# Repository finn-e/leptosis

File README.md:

# Leptosis - Ultra Flat PG1316 Split Keyboard

"Leptos" stands for "flat" in greek, added with the suffix is, it forms the word "Leptosis", signifying the most flat. This represents my long lasting desire for an real flat keyboard that is portable and light. The name is also quite similar to the latin word "levitatio", signifying levitation and thus light. (I'm bad at naming things lol)

## What is this?

Leptosis is an ultra flat split bluetooth keyboard. It's thickness will be ~7.5mm, and employs the compact miryoku layout. Using an onboard nrf module, it achieves an ultra long battery life.

| Left | Right |
| ---- | ----- |
|  |  |

## Features
- Ultra long battery life (~4 months for central and 1 year for peripheral)
- Ultra thin (7.5mm)
- Compact (13.2x9.2cm)
- Custom battery management and optimization
- Embedded nrf52 mcu
- ZMK bluetooth

## Fabrication

You can either use PCBA to fabricate the PCB, or reflow it yourself. I highly discurrage you to reflow the yourself if you haven't reflowed a aQFN package before - it's a nightmare to get right.

The PCB files are in the `hardware` directory, you need to buy one pcb for the right and the left. There is also a V-Cut panneled version in `hardware/panel`. It uses JLCPCB's 1.2mm JLC04121H-7628 stackup. Other stackups would require re-tuning of the USB data lines and antenna feed trace.

The case is in the `CAD` directory. Print out all `.step` files.

The software is in the `firmware`. Leptosis uses ZMK, allowing ultra long battery life.

After fabrication, solder on some jumpers onto the 4 test pads, and connect it to a JTAG connector (I'm using the ST-LINK). Download the bootloader from the newest action [here](https://github.com/cheyao/Adafruit_nRF52_Bootloader/actions) and unzip it.

For stlink, install openocd and run the following commands:

```zsh
openocd -f /usr/share/openocd/scripts/interface/stlink.cfg -f /usr/share/openocd/scripts/target/nrf52.cfg -c 'program <path_to_bootloader>.hex verify reset; shutdown;'
```

For other JTAG connectors, please refer to your own documentation.

Now plug in a USB-C cable, and you should see a mass storage device called `LEPTOSIS`.

Download the ZMK config from this repo: https://github.com/cheyao/zmk-config/actions, drag the utf file to the mass storage device and you are done!

## Misc

Liked this project? Drop a star and check out my [other Icepi Zero project](https://www.crowdsupply.com/icy-electronics/icepi-zero/)!

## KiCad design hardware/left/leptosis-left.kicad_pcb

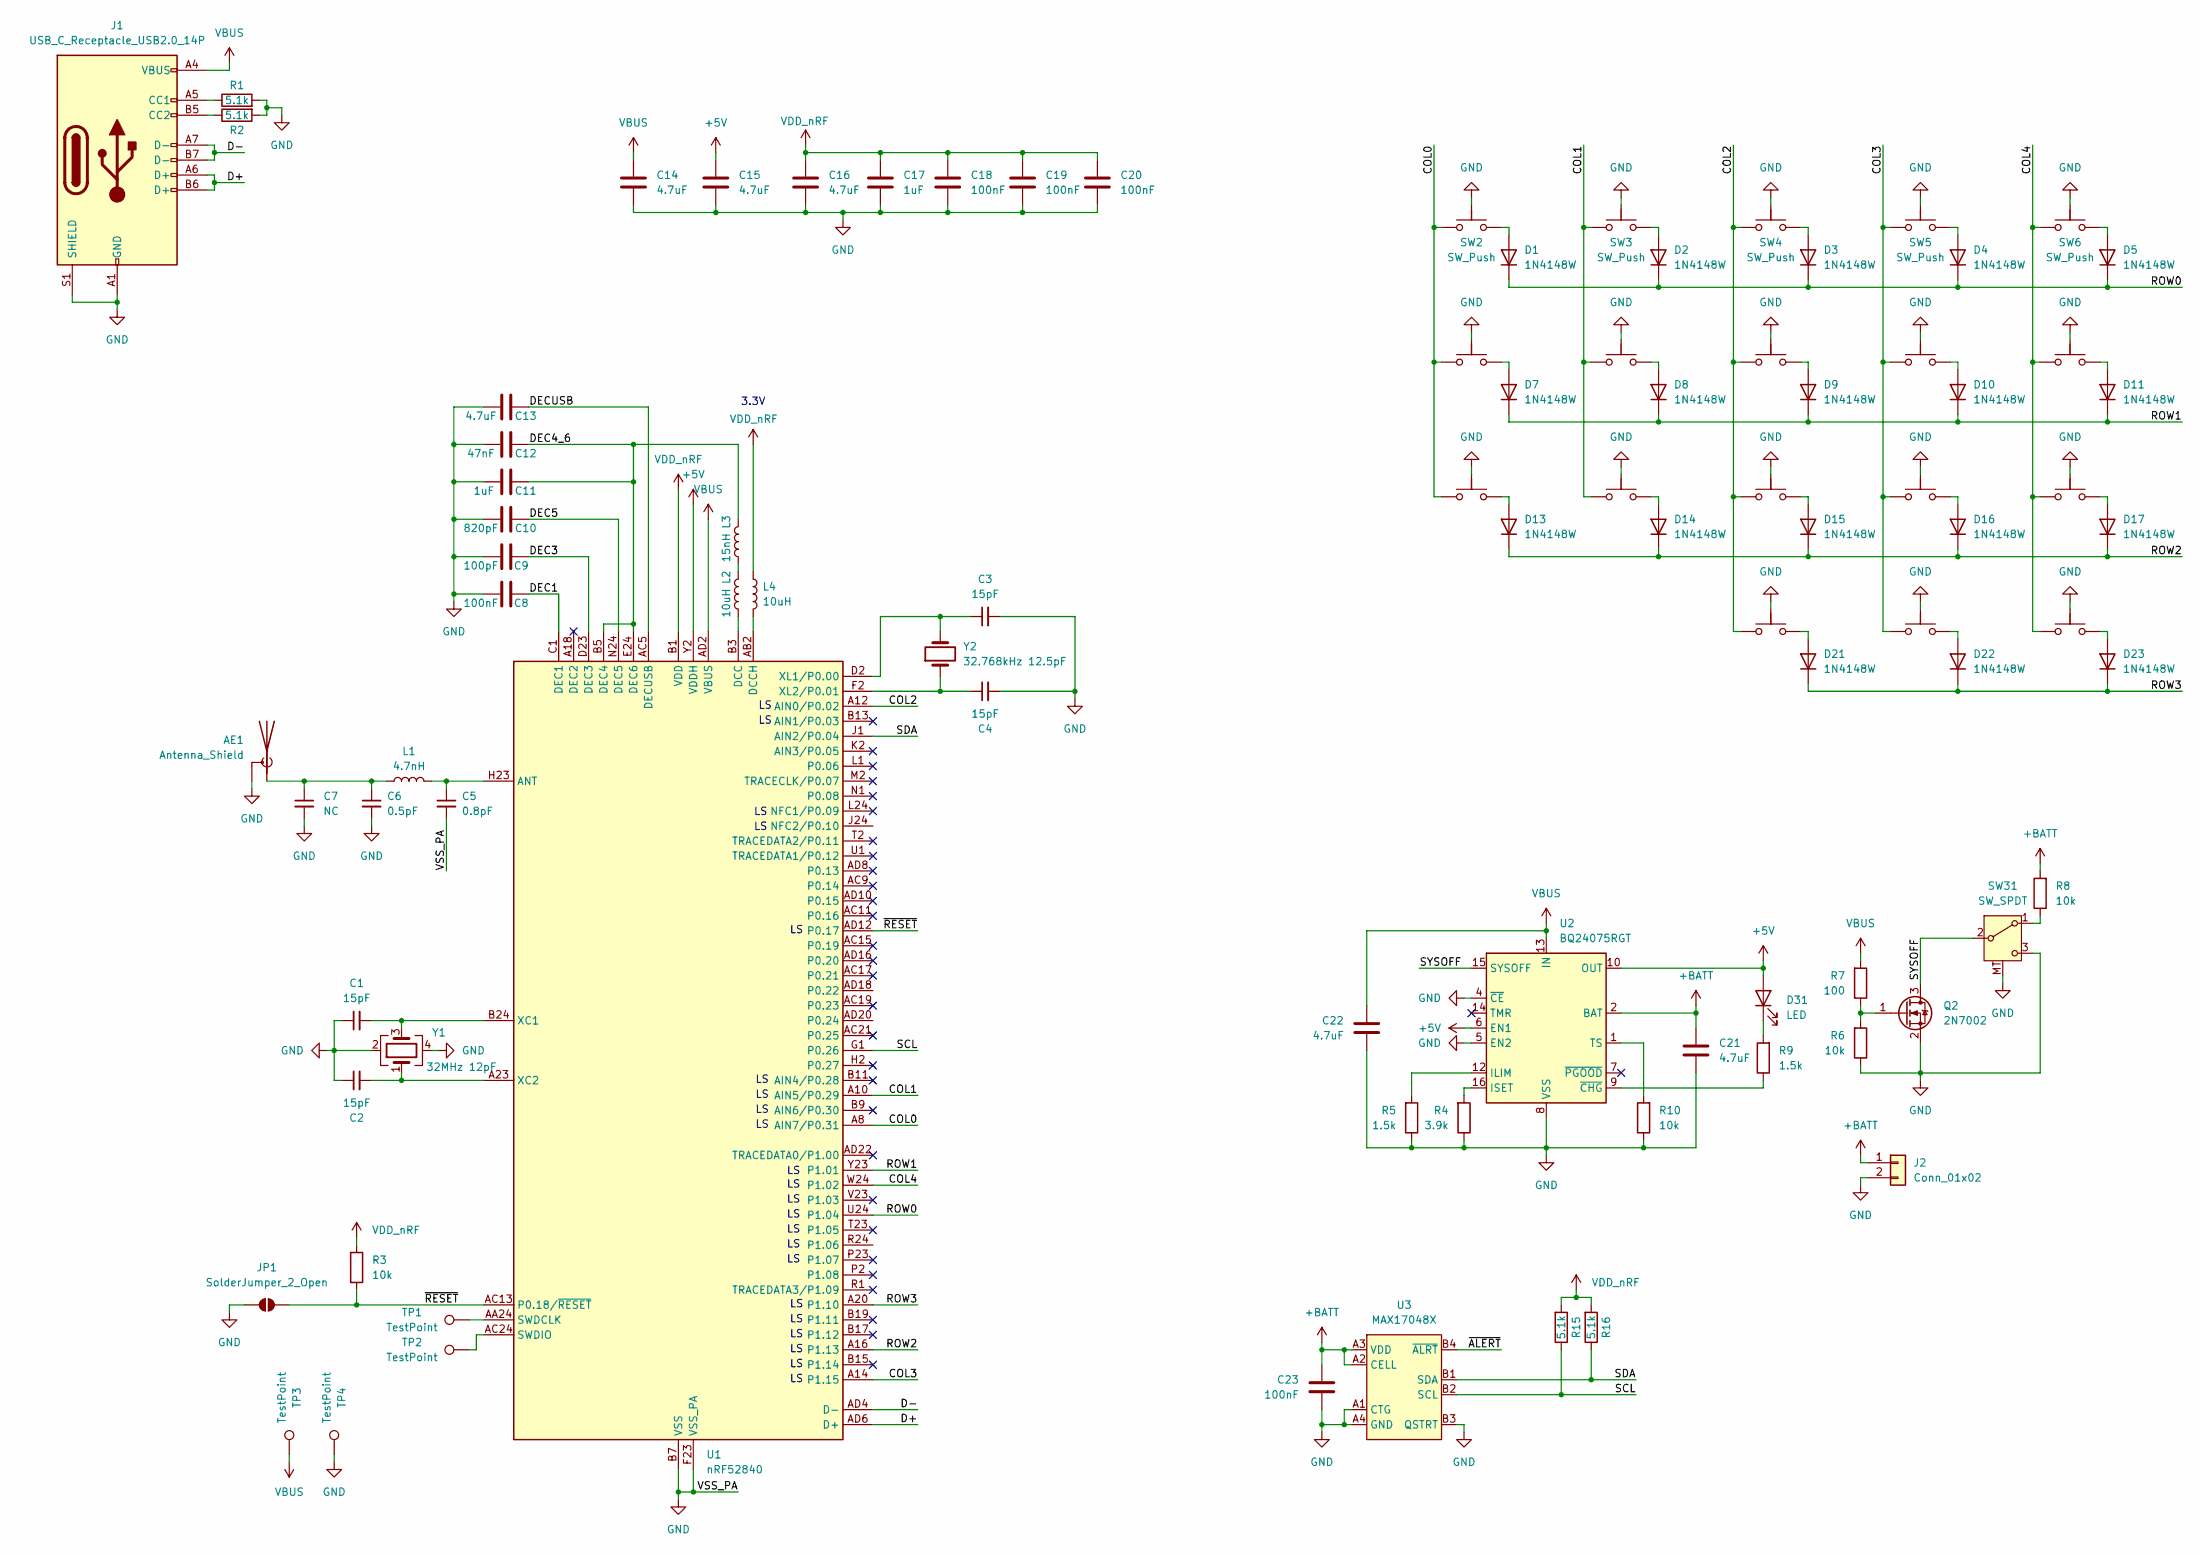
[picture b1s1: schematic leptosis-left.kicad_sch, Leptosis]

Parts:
AE1: Antenna_Shield; Texas_SWRA117D_2.4GHz_Left
C1, C2, C3, C4: 15pF; C_0402_1005Metric; LCSC Part # C1548
C5: 0.8pF; C_0402_1005Metric; LCSC Part # C41361068
C6: 0.5pF; C_0402_1005Metric; LCSC Part # C76912
C7: NC; C_0402_1005Metric
C8, C18, C19, C20, C23: 100nF; C_0402_1005Metric; LCSC Part # C1525
C9: 100pF; C_0402_1005Metric; LCSC Part # C1546
C10: 820pF; C_0402_1005Metric; LCSC Part # C107031
C11, C17: 1uF; C_0603_1608Metric; LCSC Part # C15849
C12: 47nF; C_0402_1005Metric; LCSC Part # C272875
C13, C14, C15, C16, C21, C22: 4.7uF; C_0603_1608Metric; LCSC Part # C19666
D1, D2, D3, D4, D5, D7, D8, D9, D10, D11, D13, D14, D15, D16, D17, D21, D22, D23: 1N4148W; D_SOD-123; LCSC Part # C81598
D31: LED; LED_0603_1608Metric_Pad1.05x0.95mm_HandSolder; LCSC Part # C2290
J1: USB_C_Receptacle_USB2.0_14P; USB_C_Receptacle_HRO_TYPE-C-31-M-14; LCSC Part # C223907
J2: Conn_01x02; PinSocket_1x02_P2.54mm_Vertical
JP1: SolderJumper_2_Open; SolderJumper-2_P1.3mm_Open_RoundedPad1.0x1.5mm
L1: 4.7nH; L_0402_1005Metric; LCSC Part # C86065
L2, L4: 10uH; L_0603_1608Metric; LCSC Part # C86083
L3: 15nH; L_0402_1005Metric; LCSC Part # C86059
Q2: 2N7002; SOT-23; LCSC Part # C8545
R1, R2, R15, R16: 5.1k; R_0402_1005Metric_Pad0.72x0.64mm_HandSolder; LCSC Part # C25905
R3, R6, R8, R10: 10k; R_0402_1005Metric_Pad0.72x0.64mm_HandSolder; LCSC Part # C25744
R4: 3.9k; R_0402_1005Metric_Pad0.72x0.64mm_HandSolder; LCSC Part # C131467
R5, R9: 1.5k; R_0402_1005Metric_Pad0.72x0.64mm_HandSolder; LCSC Part # C25867
R7: 100; R_0402_1005Metric_Pad0.72x0.64mm_HandSolder; LCSC Part # C25076
SW2, SW3, SW4, SW5, SW6, SW8, SW9, SW10, SW11, SW12, SW14, SW15, SW16, SW17, SW18, SW22, SW23, SW24: SW_Push; SW_PG1316S
SW31: SW_SPDT; Switch_Sink_MINI_MSK12CO2; LCSC Part # C2681570
TP1, TP2, TP3, TP4: TestPoint; TestPoint_Pad_D1.5mm
U1: nRF52840; Nordic_AQFN-73-1EP_7x7mm_P0.5mm; LCSC Part # C190794
U2: BQ24075RGT; VQFN-16-1EP_3x3mm_P0.5mm_EP1.6x1.6mm; LCSC Part # C15464
U3: MAX17048X; WLP-8_1.67x0.93_P0.4; LCSC Part # C7497002
Y1: 32MHz 12pF; Crystal_SMD_2016-4Pin_2.0x1.6mm; LCSC Part # C2682773
Y2: 32.768kHz 12.5pF; Crystal_SMD_3215-2Pin_3.2x1.5mm; LCSC Part # C5213671

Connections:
+5V: C15.1, D31.2 (A), U1.Y2 (VDDH), U2.6 (EN1), U2.10 (OUT), U2.11 (OUT)
+BATT: C21.1, C23.1, J2.1, R8.2, U2.2 (BAT), U2.3 (BAT), U3.A2 (CELL), U3.A3 (VDD)
/COL0: SW2.1, SW8.1, SW14.1, U1.A8 (AIN7/P0.31)
/COL1: SW3.1, SW9.1, SW15.1, U1.A10 (AIN5/P0.29)
/COL2: SW4.1, SW10.1, SW16.1, SW22.1, U1.A12 (AIN0/P0.02)
/COL3: SW5.1, SW11.1, SW17.1, SW23.1, U1.A14 (P1.15)
/COL4: SW6.1, SW12.1, SW18.1, SW24.1, U1.W24 (P1.02)
/D+: J1.A6 (D+), J1.B6 (D+), U1.AD6 (D+)
/D-: J1.A7 (D-), J1.B7 (D-), U1.AD4 (D-)
/DEC1: C8.2, U1.C1 (DEC1)
/DEC3: C9.2, U1.D23 (DEC3)
/DEC4_6: C11.2, C12.2, L3.2, U1.B5 (DEC4), U1.E24 (DEC6)
/DEC5: C10.2, U1.N24 (DEC5)
/DECUSB: C13.2, U1.AC5 (DECUSB)
/ROW0: D1.1 (K), D2.1 (K), D3.1 (K), D4.1 (K), D5.1 (K), U1.U24 (P1.04)
/ROW1: D7.1 (K), D8.1 (K), D9.1 (K), D10.1 (K), D11.1 (K), U1.Y23 (P1.01)
/ROW2: D13.1 (K), D14.1 (K), D15.1 (K), D16.1 (K), D17.1 (K), U1.A16 (P1.13)
/ROW3: D21.1 (K), D22.1 (K), D23.1 (K), U1.A20 (P1.10)
/SCL: R15.1, U1.G1 (P0.26), U3.B2 (SCL)
/SDA: R16.1, U1.J1 (AIN2/P0.04), U3.B1 (SDA)
/SYSOFF: Q2.3 (D), SW31.2 (B), U2.15 (SYSOFF)
/~ALERT: U3.B4 (~ALRT)
/~RESET: JP1.2 (B), R3.2, U1.AC13 (P0.18/~RESET), U1.AD12 (P0.17)
GND: AE1.2 (Shield), C1.1, C2.1, C3.2, C4.2, C5.2, C6.2, C7.2, C8.1, C9.1, C10.1, C11.1, C12.1, C13.1, C14.2, C15.2, C16.2, C17.2, C18.2, C19.2, C20.2, C21.2, C22.2, C23.2, J1.A1 (GND), J1.A12 (GND), J1.B1 (GND), J1.B12 (GND), J1.S1 (SHIELD), J2.2, JP1.1 (A), Q2.2 (S), R1.2, R2.2, R4.1, R5.1, R6.1, R10.1, SW2.MP, SW3.MP, SW4.MP, SW5.MP, SW6.MP, SW8.MP, SW9.MP, SW10.MP, SW11.MP, SW12.MP, SW14.MP, SW15.MP, SW16.MP, SW17.MP, SW18.MP, SW22.MP, SW23.MP, SW24.MP, SW31.3 (C), SW31.MT, TP4.1, U1.B7 (VSS), U1.EP (VSS), U1.F23 (VSS_PA), U2.4 (~CE), U2.5 (EN2), U2.8 (VSS), U2.17 (VSS), U3.A1 (CTG), U3.A4 (GND), U3.B3 (QSTRT), Y1.2, Y1.4
unnamed: AE1.1 (A), C6.1, C7.1, L1.1
unnamed: D1.2 (A), SW2.2
unnamed: D2.2 (A), SW3.2
unnamed: D3.2 (A), SW4.2
unnamed: D4.2 (A), SW5.2
unnamed: D5.2 (A), SW6.2
unnamed: D7.2 (A), SW8.2
unnamed: D8.2 (A), SW9.2
unnamed: D9.2 (A), SW10.2
unnamed: D10.2 (A), SW11.2
unnamed: D11.2 (A), SW12.2
unnamed: D13.2 (A), SW14.2
unnamed: D14.2 (A), SW15.2
unnamed: D15.2 (A), SW16.2
unnamed: D16.2 (A), SW17.2
unnamed: D17.2 (A), SW18.2
unnamed: D21.2 (A), SW22.2
unnamed: D22.2 (A), SW23.2
unnamed: D23.2 (A), SW24.2
unnamed: D31.1 (K), R9.2
unnamed: J1.A5 (CC1), R1.1
unnamed: J1.B5 (CC2), R2.1
unnamed: L2.2, L3.1
unnamed: Q2.1 (G), R6.2, R7.1
unnamed: R8.1, SW31.1 (A)
unnamed: C5.1, L1.2, U1.H23 (ANT)
unnamed: L2.1, U1.B3 (DCC)
unnamed: L4.1, U1.AB2 (DCCH)
unnamed: TP1.1, U1.AA24 (SWDCLK)
unnamed: TP2.1, U1.AC24 (SWDIO)
unnamed: C1.2, U1.B24 (XC1), Y1.3
unnamed: C2.2, U1.A23 (XC2), Y1.1
unnamed: C3.1, U1.D2 (XL1/P0.00), Y2.2
unnamed: C4.1, U1.F2 (XL2/P0.01), Y2.1
unnamed: R5.2, U2.12 (ILIM)
unnamed: R4.2, U2.16 (ISET)
unnamed: R10.2, U2.1 (TS)
unnamed: R9.1, U2.9 (~CHG)
VBUS: C14.1, C22.1, J1.A4 (VBUS), J1.A9 (VBUS), J1.B4 (VBUS), J1.B9 (VBUS), R7.2, TP3.1, U1.AD2 (VBUS), U2.13 (IN)
VDD_nRF: C16.1, C17.1, C18.1, C19.1, C20.1, L4.2, R3.1, R15.2, R16.2, U1.A22 (VDD), U1.AD14 (VDD), U1.AD23 (VDD), U1.B1 (VDD), U1.W1 (VDD)

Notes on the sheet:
3.3V

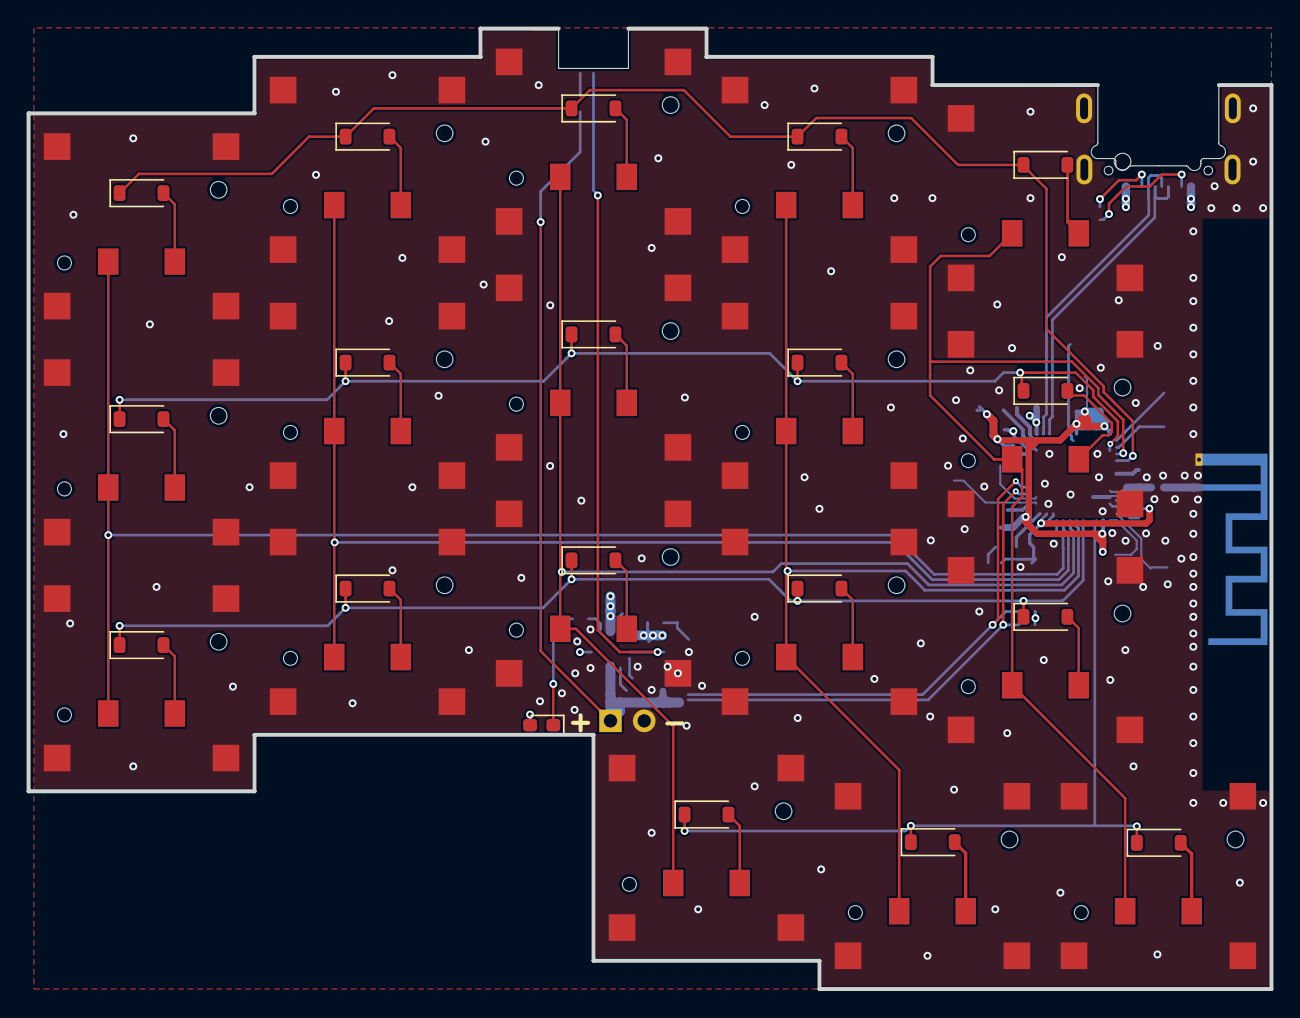
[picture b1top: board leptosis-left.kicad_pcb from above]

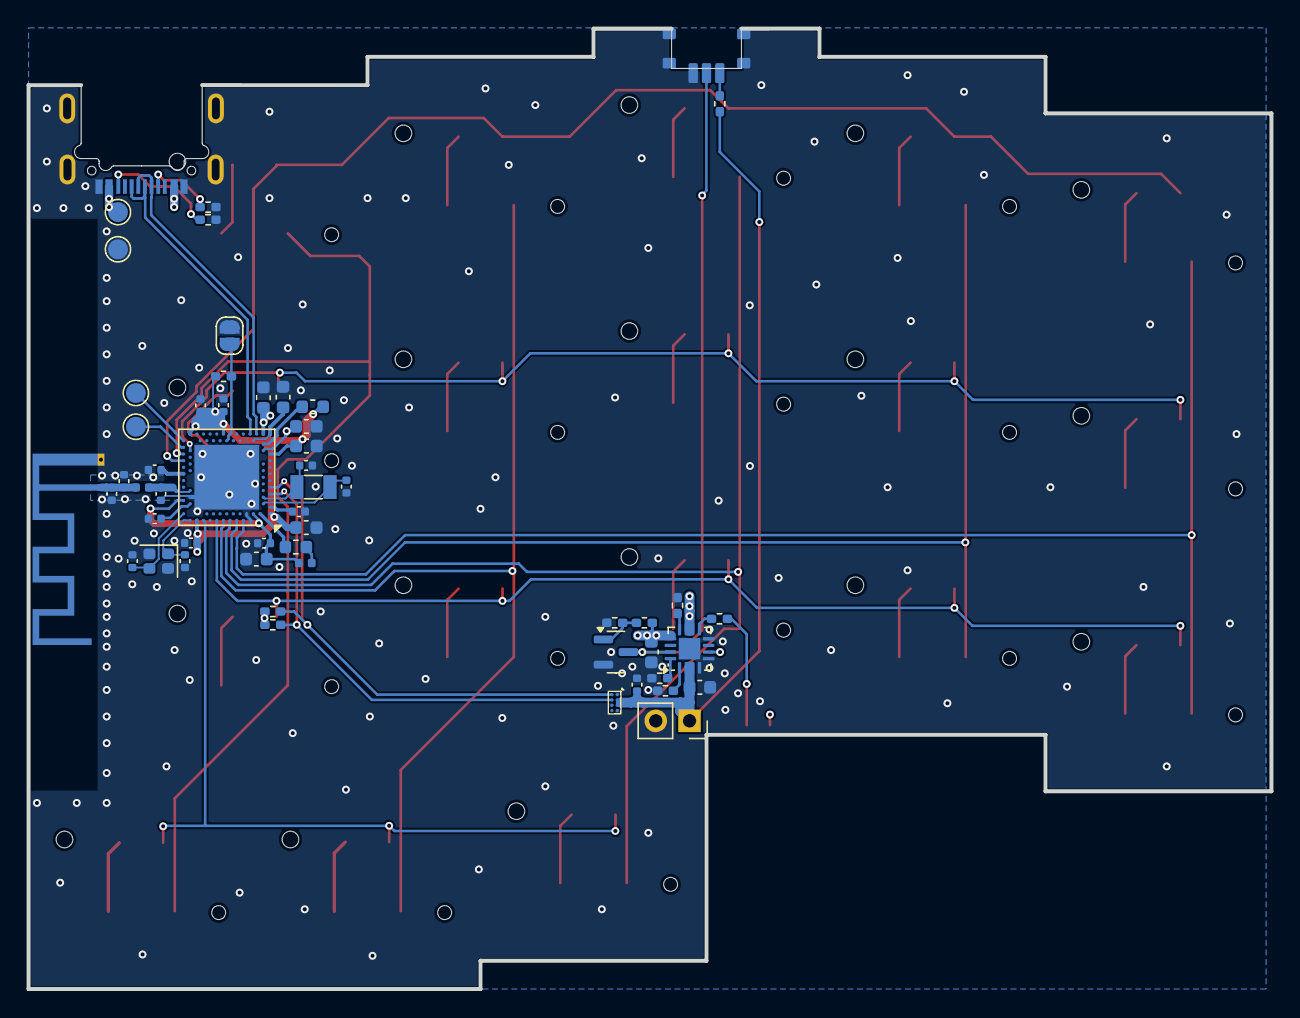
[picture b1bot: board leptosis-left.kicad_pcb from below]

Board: 4 copper layers, 93.5 x 72.3 mm, 91 parts (54 on the bottom side), 63 nets.

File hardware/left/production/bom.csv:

Designator,Footprint,Quantity,Value,LCSC Part #
"C1, C2, C3, C4",0402,4,15pF,C1548 
C10,0402,1,820pF,C107031
"C11, C17",0603,2,1uF,C15849 
C12,0402,1,47nF,C272875
"C13, C14, C15, C16, C21, C22",0603,6,4.7uF,C19666 
"C18, C19, C20, C23, C8",0402,5,100nF,C1525 
C5,0402,1,0.8pF,C41361068
C6,0402,1,0.5pF,C76912
C9,0402,1,100pF,C1546
"D1, D10, D11, D13, D14, D15, D16, D17, D2, D21, D22, D23, D3, D4, D5, D7, D8, D9",D_SOD-123,18,1N4148W,C81598
D31,0603,1,LED,C2290 
J1,USB_C_Receptacle_HRO_TYPE-C-31-M-14,1,USB_C_Receptacle_USB2.0_14P,C223907
L1,0402,1,4.7nH,C86065
"L2, L4",0603,2,10uH,C86083
L3,0402,1,15nH,C86059
Q2,SOT-23,1,2N7002,C8545
"R1, R15, R16, R2",0402,4,5.1k,C25905 
"R10, R3, R6, R8",0402,4,10k,C25744 
R4,0402,1,3.9k,C131467
"R5, R9",0402,2,1.5k,C25867 
R7,0402,1,100,C25076 
"SW10, SW11, SW12, SW14, SW15, SW16, SW17, SW18, SW2, SW22, SW23, SW24, SW3, SW4, SW5, SW6, SW8, SW9",SW_PG1316S,18,SW_Push,
SW31,Switch_Sink_MINI_MSK12CO2,1,SW_SPDT,C2681570 
U1,Nordic_AQFN-73-1EP_7x7mm_P0.5mm,1,nRF52840,C190794
U2,VQFN-16-1EP_3x3mm_P0.5mm_EP1.6x1.6mm,1,BQ24075RGT,C15464
U3,WLP-8_1.67x0.93_P0.4,1,MAX17048X,C7497002
Y1,Crystal_SMD_2016-4Pin_2.0x1.6mm,1,32MHz 12pF,C2682773
Y2,Crystal_SMD_3215-2Pin_3.2x1.5mm,1,32.768kHz 12.5pF,C5213671

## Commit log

2025-06-23 Init
2025-06-26 Finish most of schem
2025-06-28 2 Layers
2025-06-29 Case
2025-07-06 Split keeb!
2025-08-07 Finished!
2025-09-07 Finish
2025-09-07 Add permissive solderpad license
2025-09-10 Oppsie typo :sob:
2025-09-26 Fix typo
